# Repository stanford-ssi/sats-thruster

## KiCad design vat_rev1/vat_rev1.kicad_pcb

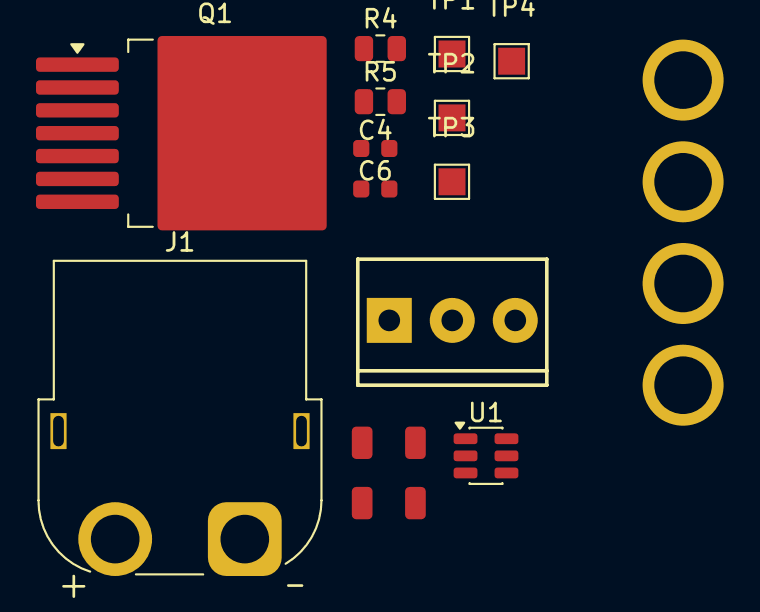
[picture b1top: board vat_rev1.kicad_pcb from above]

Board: 2 copper layers, 18 parts (0 on the bottom side), 8 nets, no tracks yet.

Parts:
C3, C5: 1uF; C_1206
C4, C6: 0.1uF; C_0603
H1, H2, H3, H4: MountingHole_Pad; MountingHole_3.2mm_M3_DIN965_PadMOD
J1: MAG_NOZZLE; AMASS_XT60PW-F_1x02_P7.20mm_Horizontal
JP1: Jumper_3_Open; ScrewTerminal_1x03_P3.5mm_Horizontal_Black
Q1: IPB017N10N5ATMA1; TO-263-7_TabPin4
R4, R5: 4.7; R_0805_2012Metric
TP1, TP2, TP3, TP4: TestPoint; TestPoint_Pad_1.5x1.5mm
U1: 1EDN8550B; SOT-23-6

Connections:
CL_SW: J1.2, Q1.1 (D), TP4.1 (1_1)
GND: C3.2, C4.2, C5.2, C6.2, H1.1 (1_1), H2.1 (1_1), H3.1 (1_1), H4.1 (1_1), U1.2 (GND)
unnamed: Q1.2 (G), R4.2, R5.2
unnamed: R4.1, U1.6 (OUT_SNK)
unnamed: R5.1, U1.5 (OUT_SRC)
VBUS: C5.1, C6.1, JP1.1 (A), U1.4 (VDD)
V_COIL: C3.1, C4.1, J1.1, JP1.2 (C), TP3.1 (1_1)
V_REG: JP1.3 (B), TP1.1 (1_1)

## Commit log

2026-04-18 vat_rev1 kicad files
2026-04-18 added msg
2026-04-21 put some things
2026-05-19 I think its mostly chilling
